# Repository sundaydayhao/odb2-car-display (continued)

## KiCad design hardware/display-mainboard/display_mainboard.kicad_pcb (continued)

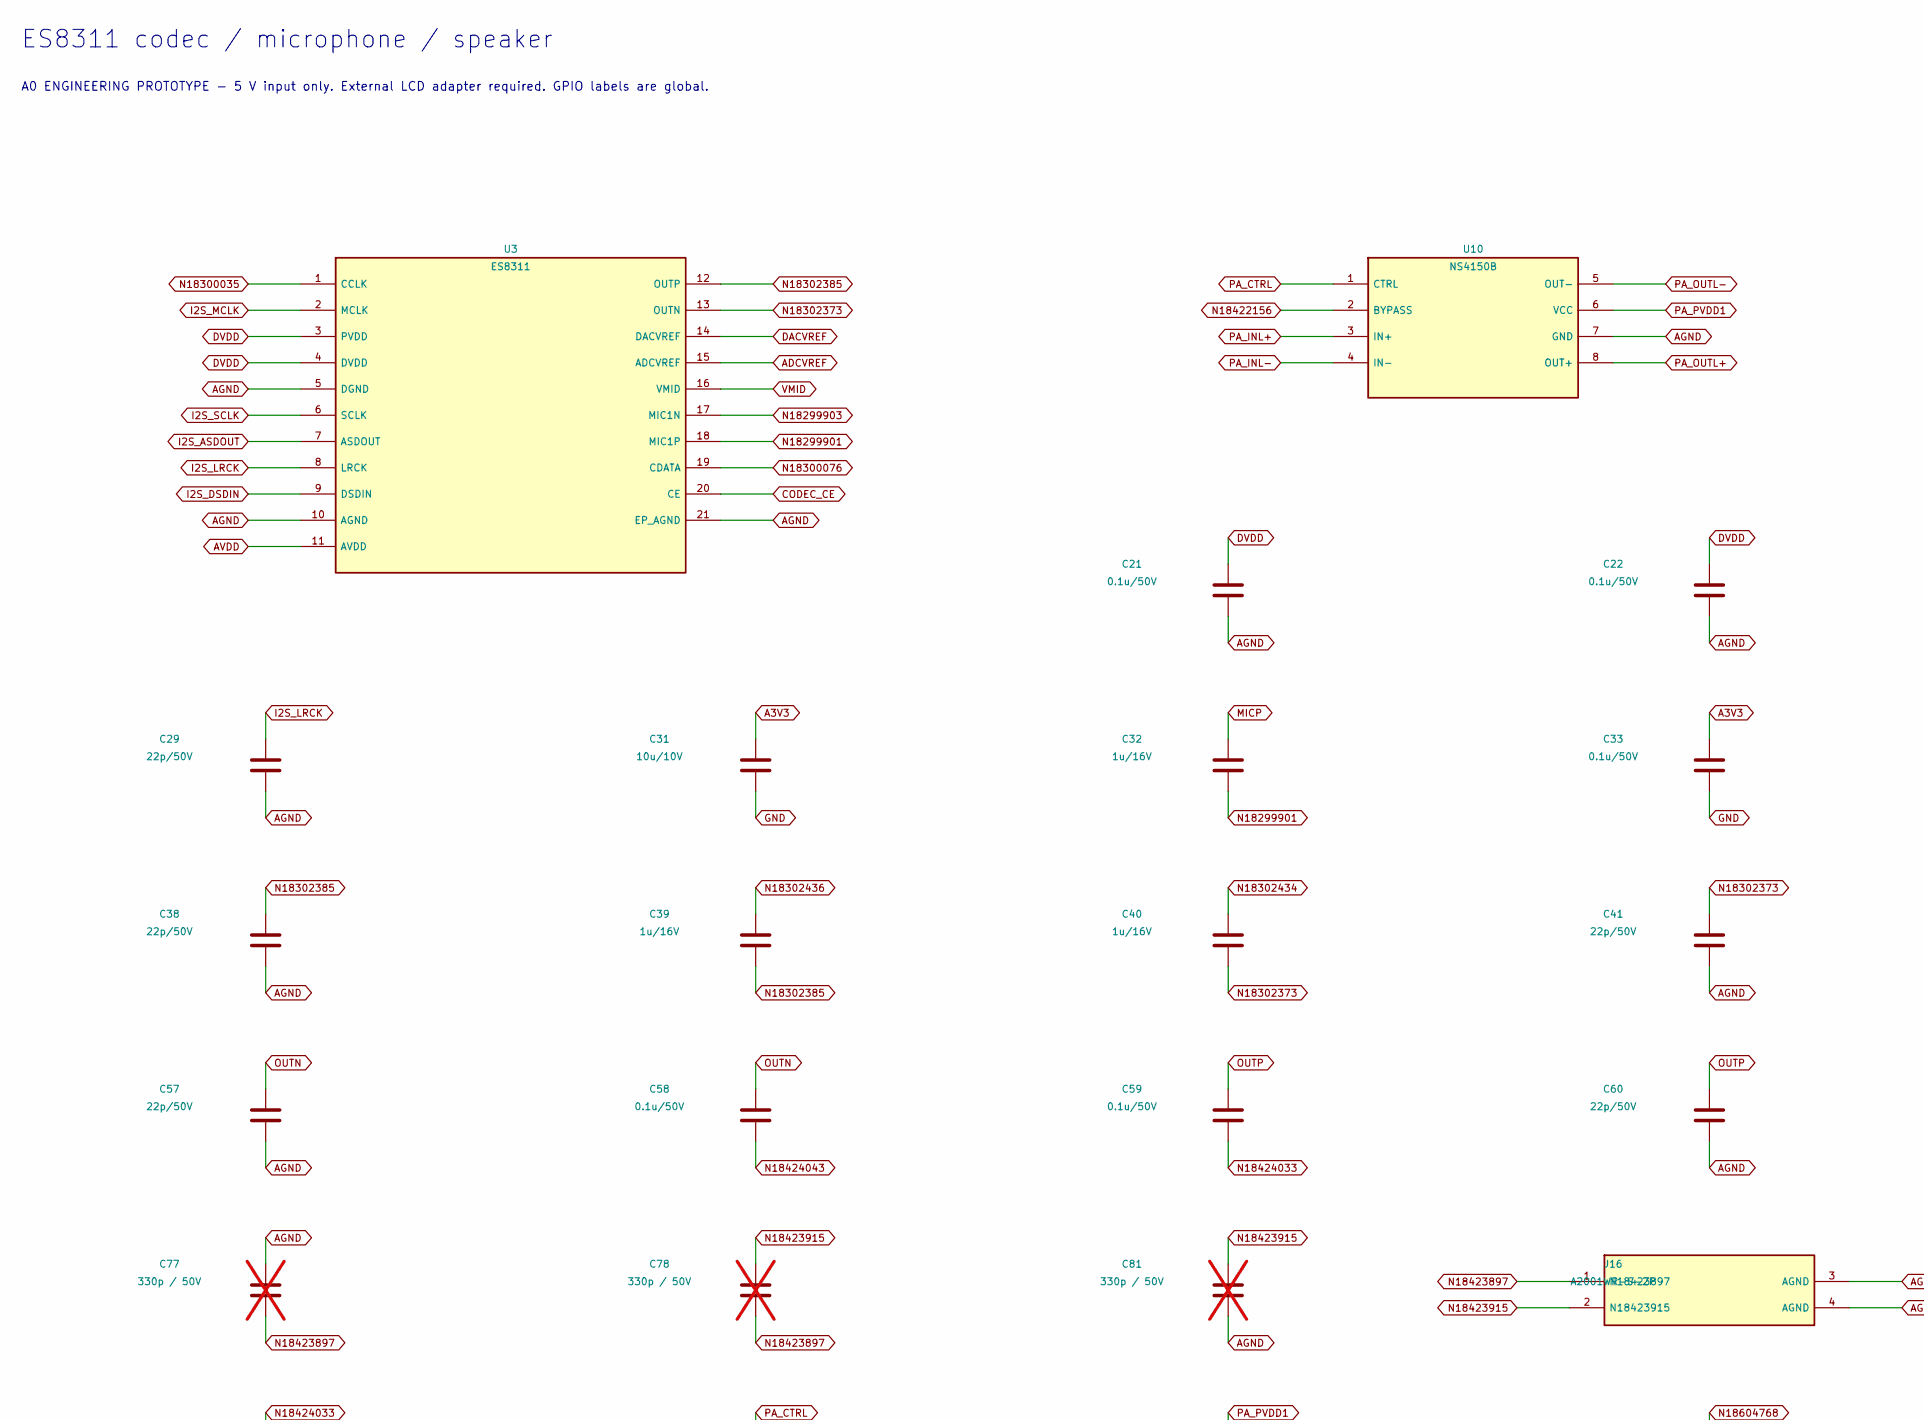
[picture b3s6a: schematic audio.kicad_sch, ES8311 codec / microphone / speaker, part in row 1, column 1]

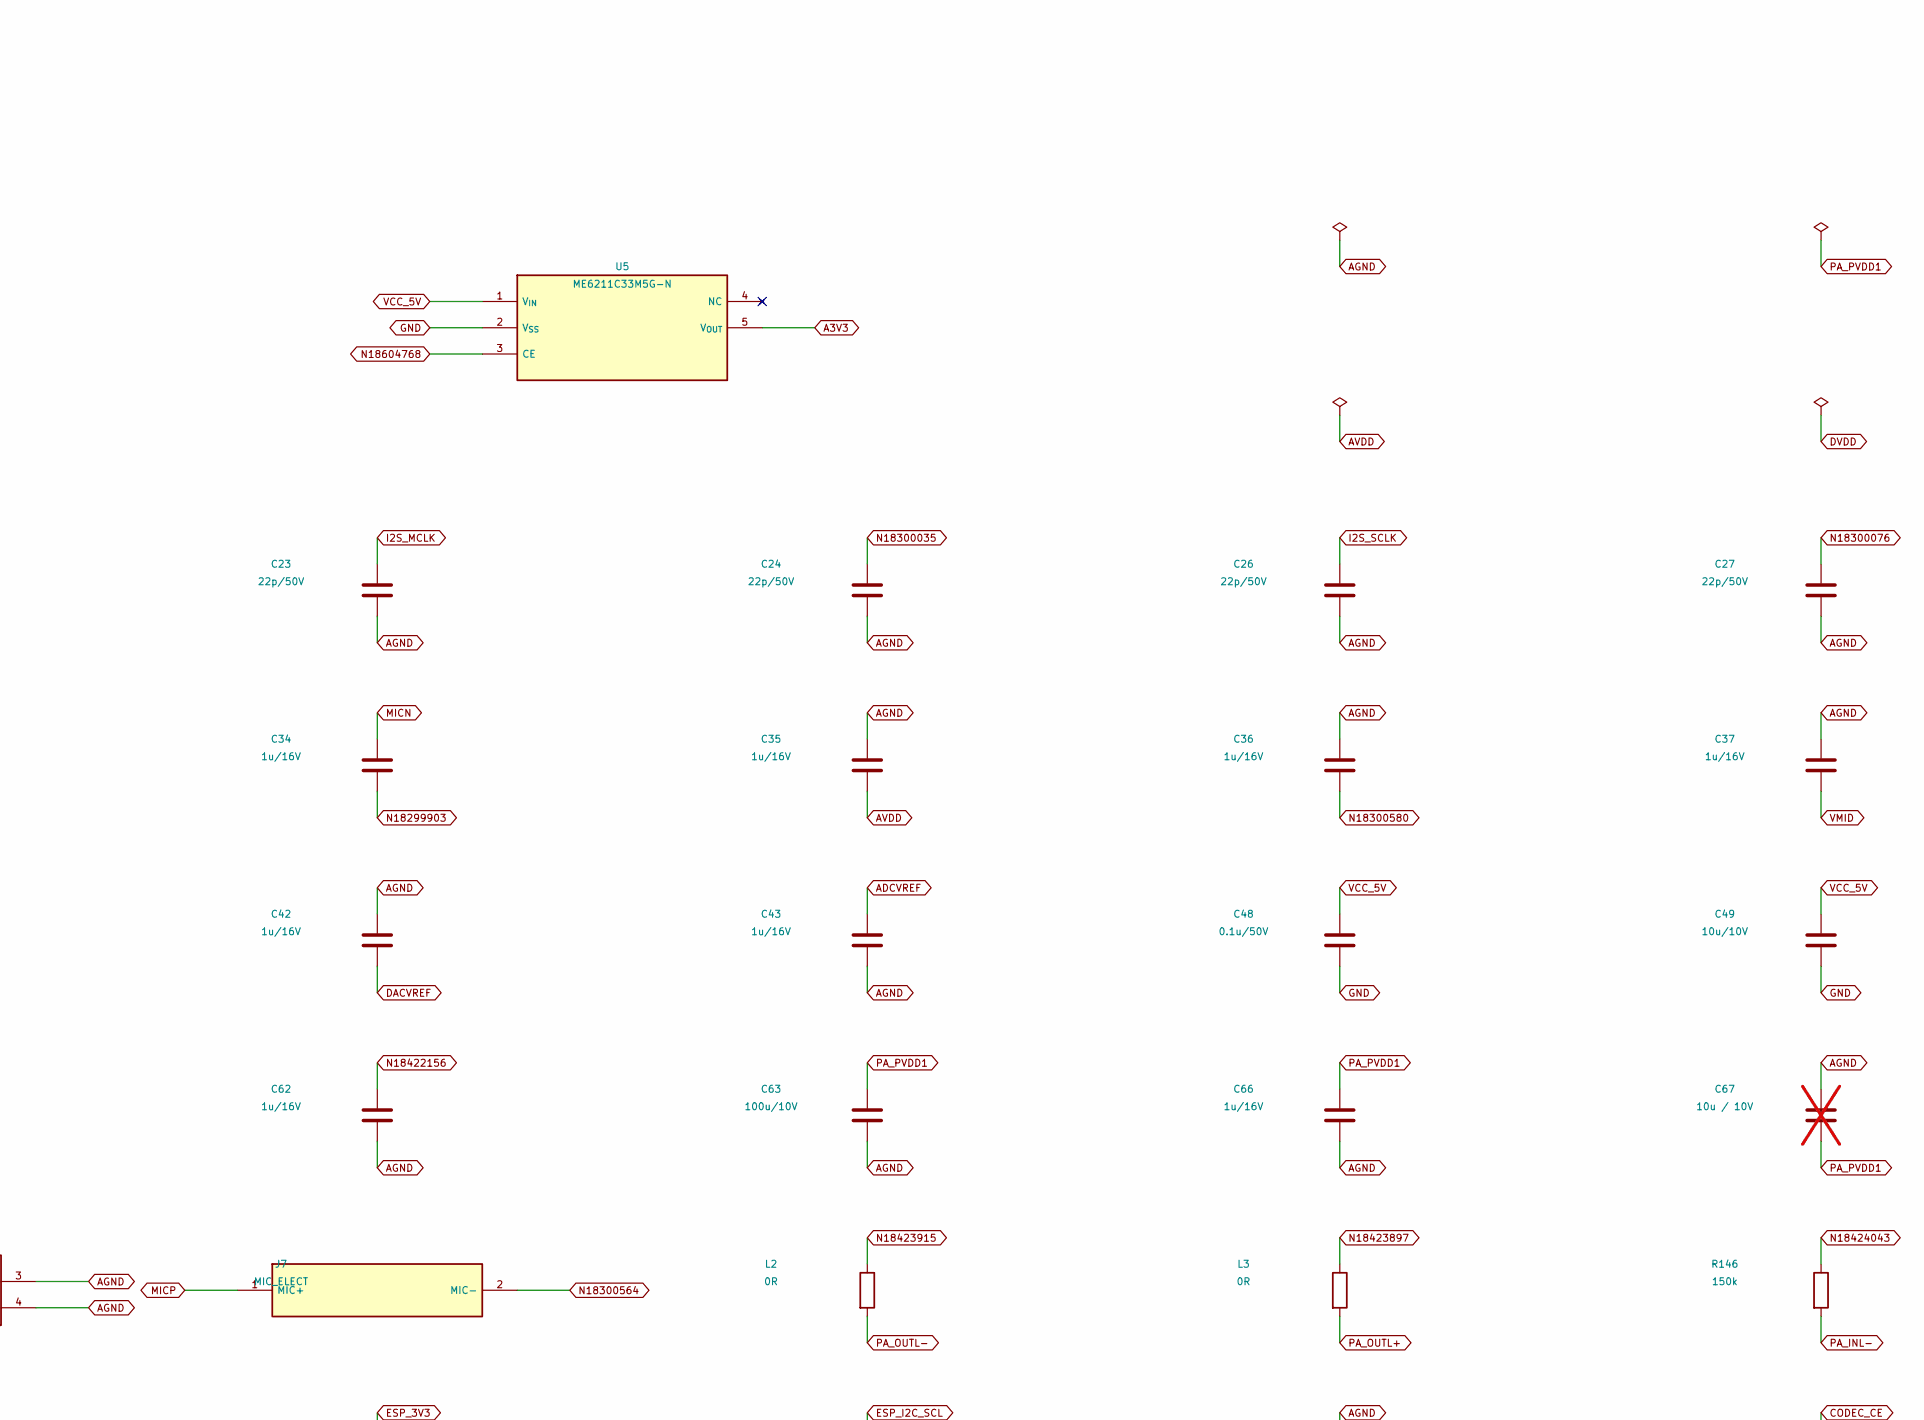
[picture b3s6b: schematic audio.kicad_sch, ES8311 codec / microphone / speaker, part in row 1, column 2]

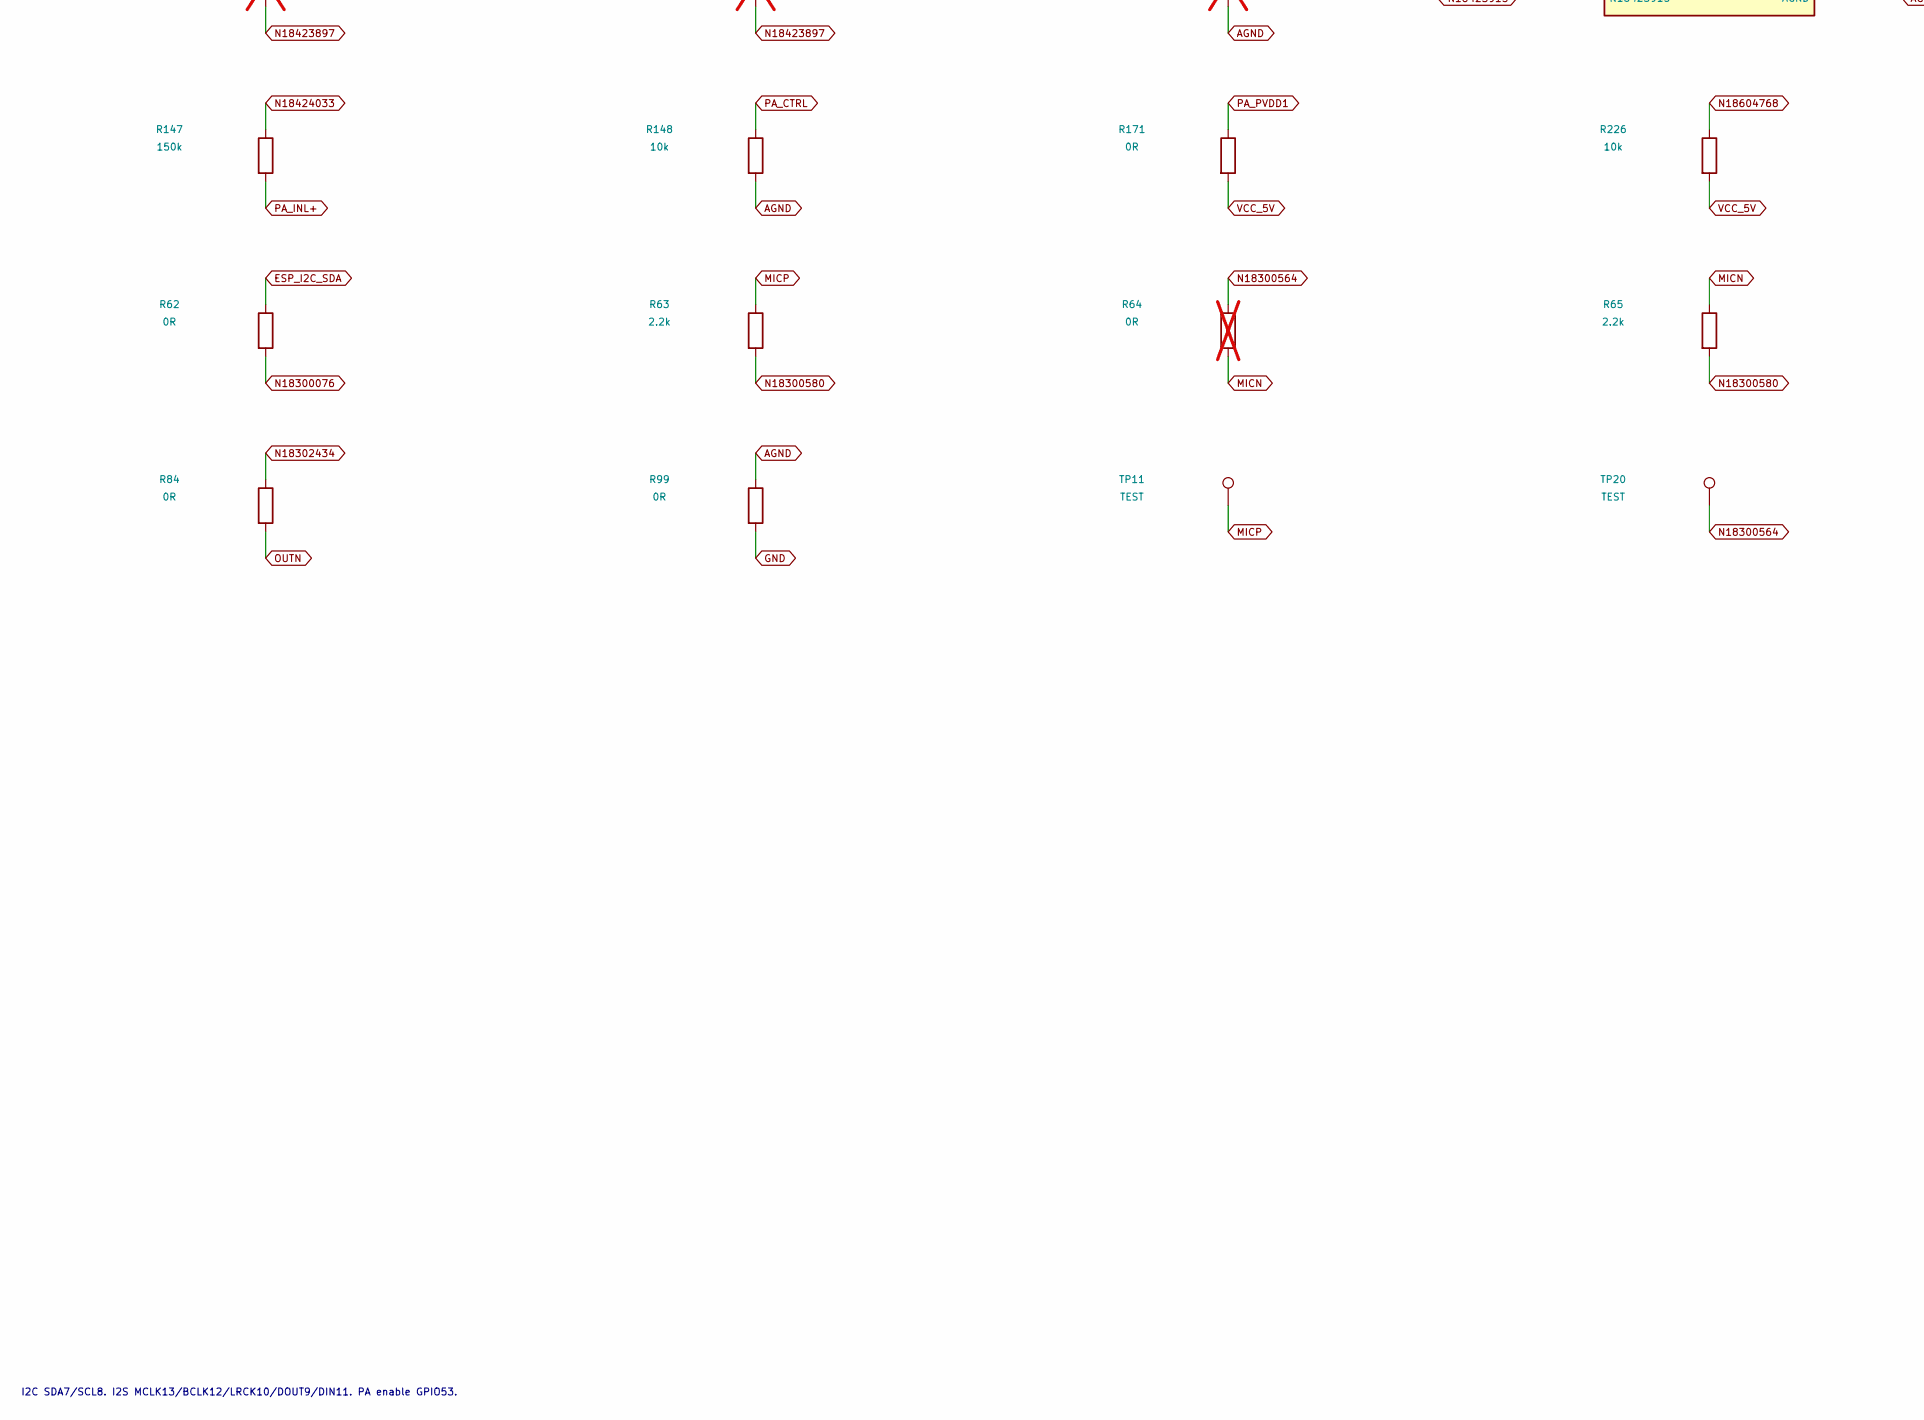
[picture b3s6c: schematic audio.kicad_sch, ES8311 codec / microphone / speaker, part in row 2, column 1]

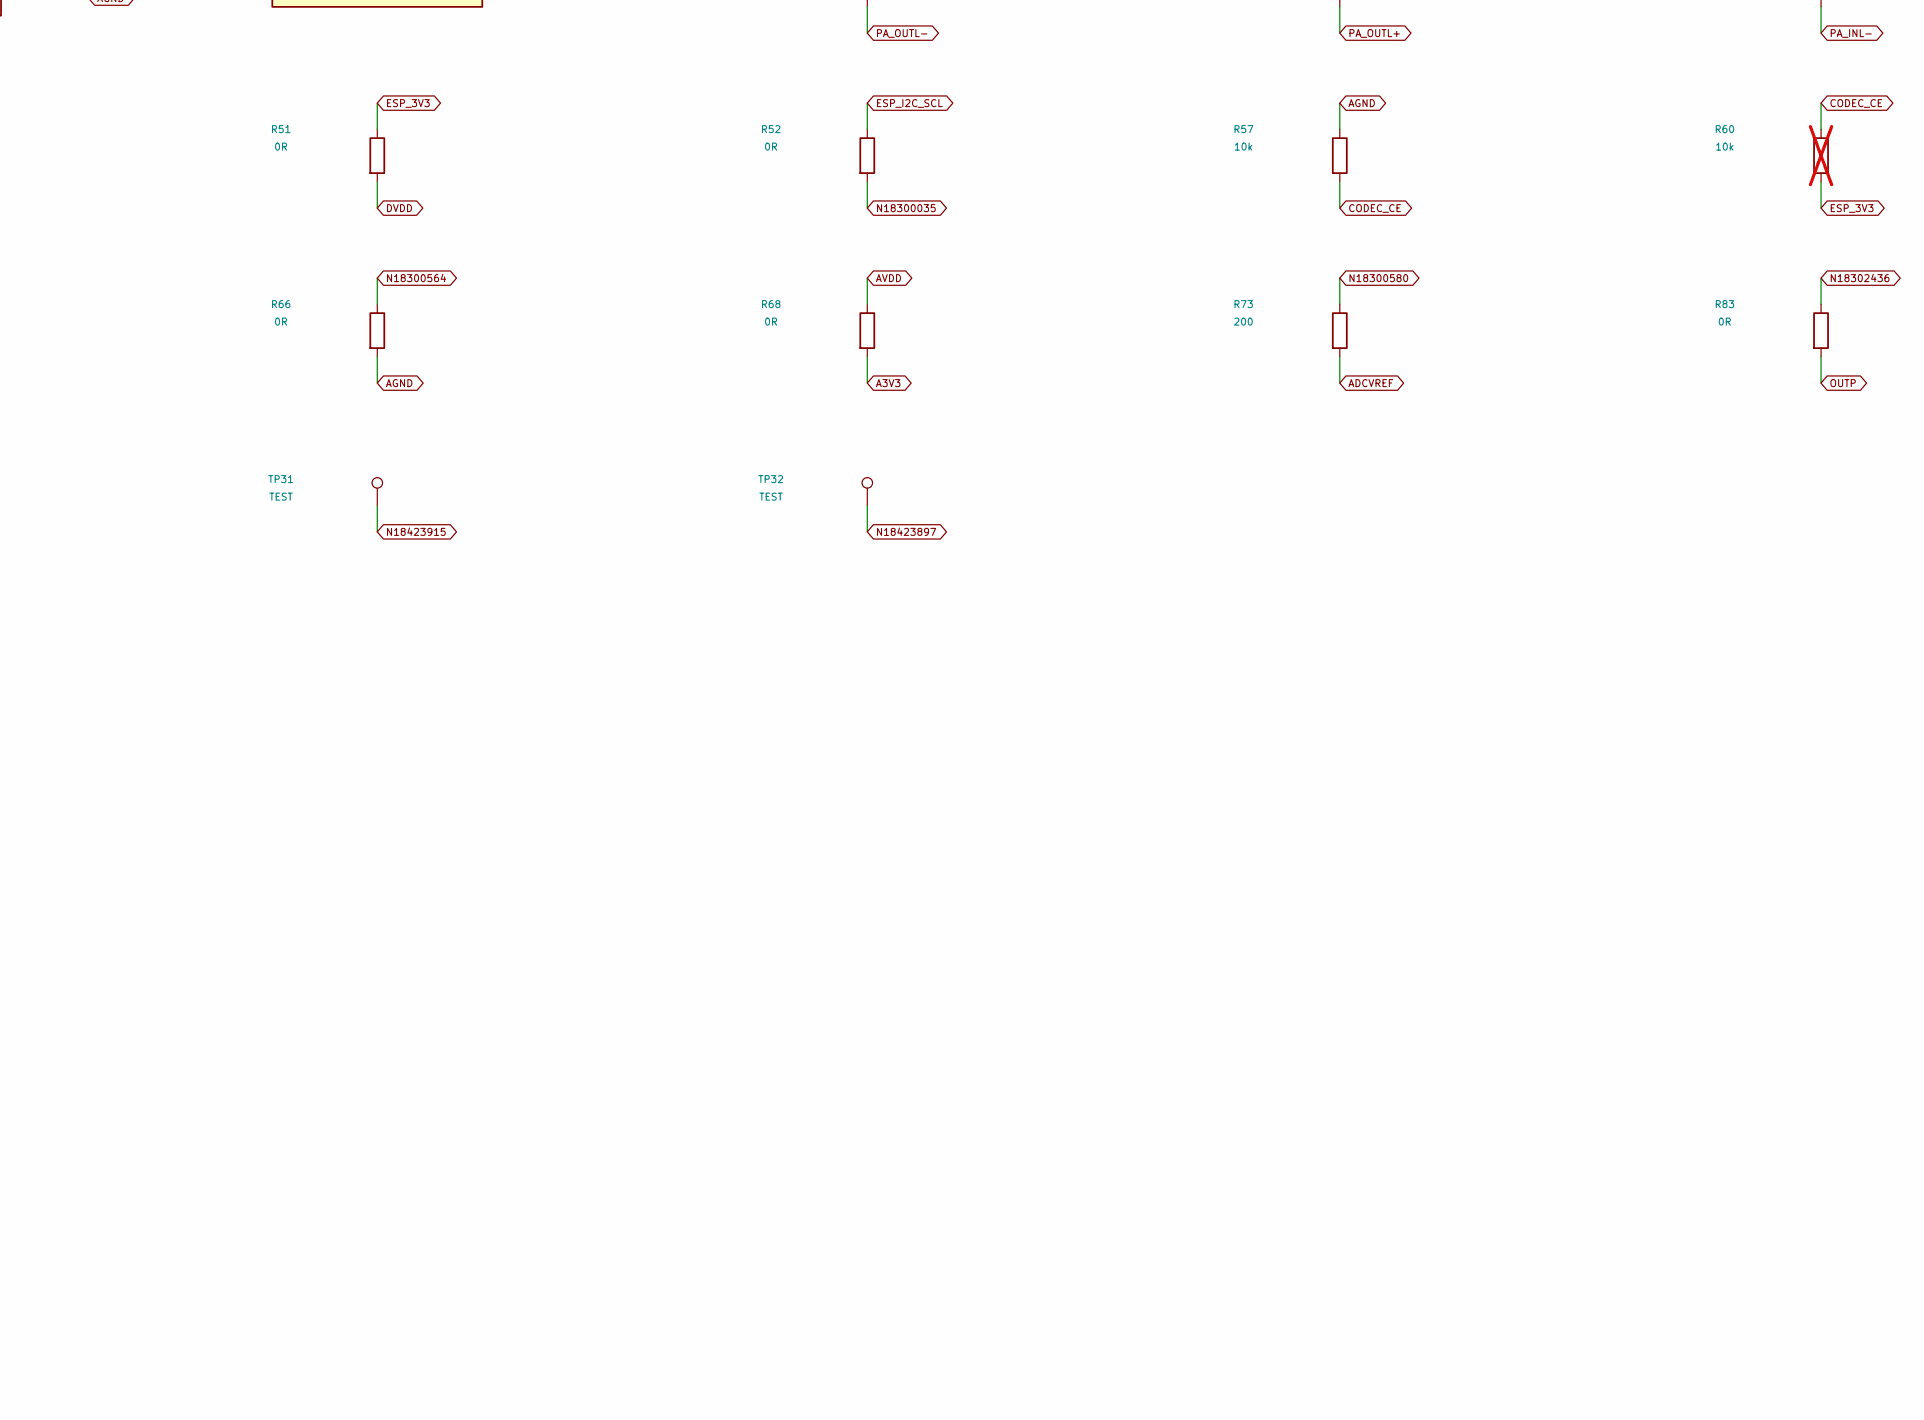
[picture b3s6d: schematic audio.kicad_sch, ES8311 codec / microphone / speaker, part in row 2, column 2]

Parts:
C21, C22, C33, C48, C58, C59: 0.1u/50V; C0402__d1e3d90c7a
C23, C24, C26, C27, C29, C38, C41, C57, C60: 22p/50V; C0402__d1e3d90c7a
C31, C49: 10u/10V; C0603__ebd4ddd8e4
C32, C34, C35, C36, C37, C39, C40, C42, C43, C62, C66: 1u/16V; C0402__d1e3d90c7a
C63: 100u/10V; C1206__33617ed97b
C67: 10u / 10V; C0603__ebd4ddd8e4; not fitted
C77, C78, C81: 330p / 50V; C0402__d1e3d90c7a; not fitted
J7: MIC_ELECT; MIC2_4_B4013AM422-042__565a78fc3e; MPN B4013AM422-042
J16: A2001WR-S-2P; CON2X1_2P0_SMT_PH2A-S-A__3aafb2579c; MPN A2001WR-S-2P
L2, L3: 0R; R0603__9e2f069e96
R51, R52, R62, R66, R68, R83, R84: 0R; R0402__c67fe31f10
R57, R148, R226: 10k; R0402__c67fe31f10
R60: 10k; R0402__c67fe31f10; not fitted
R63, R65: 2.2k; R0402__c67fe31f10
R64: 0R; R0402__c67fe31f10; not fitted
R73: 200; R0402__c67fe31f10
R99, R171: 0R; R0603__9e2f069e96
R146, R147: 150k; R0402__c67fe31f10
TP11, TP20, TP31, TP32: TEST; TPC1__9f0857eafe
U3: ES8311; QFN20_0P4_3__b115faeb64; MPN ES8311
U5: ME6211C33M5G-N; SOT23-5__cf243f5b81; MPN ME6211C33M5G-N
U10: NS4150B; SSOP8_0P65_5__11bfe522a4; MPN NS4150B

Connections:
A3V3: C31.1, C33.1, R68.2, U5.5 (V_{OUT})
ADCVREF: C43.1, R73.2, U3.15 (ADCVREF)
AGND: C21.2, C22.2, C23.2, C24.2, C26.2, C27.2, C29.2, C35.1, C36.1, C37.1, C38.2, C41.2, C42.1, C43.2, C57.2, C60.2, C62.2, C63.2, C66.2, C67.1, C77.1, C81.2, J16.3 (AGND), J16.4 (AGND), R57.1, R66.2, R99.1, R148.2, U3.5 (DGND), U3.10 (AGND), U3.21 (EP_AGND), U10.7 (GND)
AVDD: C35.2, R68.1, U3.11 (AVDD)
CODEC_CE: R57.2, R60.1, U3.20 (CE)
DACVREF: C42.2, U3.14 (DACVREF)
DVDD: C21.1, C22.1, R51.2, U3.3 (PVDD), U3.4 (DVDD)
ESP_3V3: R51.1, R60.2; also elsewhere on the board
ESP_I2C_SCL: R52.1; also elsewhere on the board
ESP_I2C_SDA: R62.1; also elsewhere on the board
I2S_ASDOUT: U3.7 (ASDOUT); also elsewhere on the board
I2S_DSDIN: U3.9 (DSDIN); also elsewhere on the board
I2S_LRCK: C29.1, U3.8 (LRCK); also elsewhere on the board
I2S_MCLK: C23.1, U3.2 (MCLK); also elsewhere on the board
I2S_SCLK: C26.1, U3.6 (SCLK); also elsewhere on the board
MICN: C34.1, R64.2, R65.1
MICP: C32.1, J7.1 (MIC+), R63.1, TP11.1
N18299901: C32.2, U3.18 (MIC1P)
N18299903: C34.2, U3.17 (MIC1N)
N18300035: C24.1, R52.2, U3.1 (CCLK)
N18300076: C27.1, R62.2, U3.19 (CDATA)
N18300564: J7.2 (MIC-), R64.1, R66.1, TP20.1
N18300580: C36.2, R63.2, R65.2, R73.1
N18302373: C40.2, C41.1, U3.13 (OUTN)
N18302385: C38.1, C39.2, U3.12 (OUTP)
N18302434: C40.1, R84.1
N18302436: C39.1, R83.1
N18422156: C62.1, U10.2 (BYPASS)
N18423897: C77.2, C78.2, J16.1 (N18423897), L3.1, TP32.1
N18423915: C78.1, C81.1, J16.2 (N18423915), L2.1, TP31.1
N18424033: C59.2, R147.1
N18424043: C58.2, R146.1
N18604768: R226.1, U5.3 (CE)
OUTN: C57.1, C58.1, R84.2
OUTP: C59.1, C60.1, R83.2
PA_CTRL: R148.1, U10.1 (CTRL); also elsewhere on the board
PA_INL+: R147.2, U10.3 (IN+)
PA_INL-: R146.2, U10.4 (IN-)
PA_OUTL+: L3.2, U10.8 (OUT+)
PA_OUTL-: L2.2, U10.5 (OUT-)
PA_PVDD1: C63.1, C66.1, C67.2, R171.1, U10.6 (VCC)
VCC_5V: C48.1, C49.1, R171.2, R226.2, U5.1 (V_{IN}); also elsewhere on the board
VMID: C37.2, U3.16 (VMID)

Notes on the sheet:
ES8311 codec / microphone / speaker
A0 ENGINEERING PROTOTYPE - 5 V input only. External LCD adapter required. GPIO labels are global.
I2C SDA7/SCL8. I2S MCLK13/BCLK12/LRCK10/DOUT9/DIN11. PA enable GPIO53.

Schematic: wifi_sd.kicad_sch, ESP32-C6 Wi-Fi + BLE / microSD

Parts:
C1: 10u/10V; C0603__1e7c8298a8
C2: 0.1u/50V; C0402__df1ad35910
C8: 1u/16V; C0402__df1ad35910
C14: 0.1u/50V; C0402_097d4b0b__328ab4e626
C15: 10u/10V; C0603_1ead970f__4ff9dc89d7
D3, D4, D5, D6, D7, D8, D10, D11: BSDFN2C031U; SOD882_55527cd7__832596a649; MPN BSDFN2C031U
J2: CON3X2; CON3X2_2P54__5709bcd3ab
J21: TF_CARD; TF_CARDA__9ea14d9044; MPN TF-1007F
Q8: AO3401A; SOT23-3__14816d8467; MPN AO3401A
R1, R3, R5, R6, R11, R12: 51k; R0402__6ca295102a
R4, R10: 10k; R0402__6ca295102a
R16, R17, R19, R21, R34, R36: 51k; R0402_097d4b0b__c1bfdfccc2
R229: 10k; R0402_097d4b0b__c1bfdfccc2
R230: 10k; R0402_097d4b0b__c1bfdfccc2; not fitted
TP3, TP4, TP5, TP6, TP7, TP8, TP9, TP13: TEST; TPC1_fd69f0aa__930cba657a
TP10, TP12, TP14, TP15, TP16, TP17, TP18, TP19: TEST; TPC1__56d55e75a0
U1: ESP32-C6-MINI-1; ESP32-C6-MINI-1__12b1335637; MPN ESP32-C6-MINI-1-N4

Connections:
C6_EN: C8.1, J2.1 (C6_EN), R4.1, U1.8 (EN); also elsewhere on the board
C6_IO8: R10.1, U1.22 (GPIO8)
C6_IO9: J2.6 (C6_IO9), U1.23 (GPIO9)
C6_U0RXD: J2.5 (C6_U0RXD), U1.30 (U0RXD)
C6_U0TXD: J2.3 (C6_U0TXD), U1.31 (U0TXD)
C6_WAKEUP: U1.5 (GPIO2); also elsewhere on the board
ESP_3V3: C1.1, C2.1, Q8.2 (S), R1.1, R3.1, R4.2, R5.1, R6.1, R10.2, R11.1, R12.1, R230.2, U1.3 (3V3); also elsewhere on the board
ESP_LDO_VO4: R17.1, R19.1, R21.1, R34.1, R36.1; also elsewhere on the board
SD1_CLK: D6.2 (A2), J21.5 (SD1_CLK), TP15.1; also elsewhere on the board
SD1_CMD: D4.2 (A2), J21.3 (SD1_CMD), R17.2, TP14.1; also elsewhere on the board
SD1_D0: D11.2 (A2), J21.7 (SD1_D0), R36.2, TP19.1; also elsewhere on the board
SD1_D1: D10.2 (A2), J21.8 (SD1_D1), R34.2, TP18.1; also elsewhere on the board
SD1_D2: D8.2 (A2), J21.1 (SD1_D2), R21.2, TP17.1; also elsewhere on the board
SD1_D3: D7.2 (A2), J21.2 (SD1_D3), R19.2, TP16.1; also elsewhere on the board
SD1_VDD: C14.1, C15.1, D3.2 (A2), J21.4 (SD1_VDD), Q8.3 (D), R16.1, TP13.1
SD2_CLK: R12.2, TP5.1, U1.25 (GPIO19); also elsewhere on the board
SD2_CMD: R11.2, TP4.1, U1.24 (GPIO18); also elsewhere on the board
SD2_D0: R6.2, TP9.1, U1.26 (GPIO20); also elsewhere on the board
SD2_D1: R5.2, TP8.1, U1.27 (GPIO21); also elsewhere on the board
SD2_D2: R3.2, TP7.1, U1.28 (GPIO22); also elsewhere on the board
SD2_D3: R1.2, TP6.1, U1.29 (GPIO23); also elsewhere on the board
SD_DET: D5.2 (A2), J21.9 (SD_DET), R16.2, TP10.1
SD_PWRN: Q8.1 (G), R229.2, R230.1; also elsewhere on the board

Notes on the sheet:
ESP32-C6 Wi-Fi + BLE / microSD
A6 MIPI SINGLE PCB - Regulated 5 V only. LCD / I2C CTP connect directly. GPIO labels are global.
microSD power switch (Q8 / GPIO45 active-low); C1 is C6 input decoupling. Retained in A4.

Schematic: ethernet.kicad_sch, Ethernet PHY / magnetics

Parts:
C1: 10u/10V; C0603__ebd4ddd8e4
C64, C68: 20p/50V; C0402__d1e3d90c7a
C108, C113, C114: 10u/10V; C0603_1ead970f__97efe4e755
C109, C111, C112, C115, C116: 0.1u/50V; C0402_097d4b0b__369f5d8838
J17: RJ45_HR913550A; RJ45_HR913129A__640c741964; MPN HR913550A
Q8: AO3401A; SOT23-3__4e657f28a8; MPN AO3401A
R139, R142, R143, R144, R150, R158, R161: 0R; R0402__c67fe31f10
R140, R141, R149, R155, R157, R169: 5.1k; R0402__c67fe31f10
R153, R154, R156, R164, R168: 5.1k; R0402__c67fe31f10; not fitted
R159: 10M; R0402__c67fe31f10; not fitted
R160: 1.5k; R0402__c67fe31f10; not fitted
R163: 1.5k; R0402__c67fe31f10
R165: 6.19k; R0402__c67fe31f10
R166, R167: 10k; R0402__c67fe31f10; not fitted
R181: 0R; R0603__9e2f069e96
R213: 0R; R0603_1ead970f__b0e26ec379
R222, R223: 1k; R0402_097d4b0b__cc2a00f46d
R229: 10k; R0402_097d4b0b__cc2a00f46d
R230: 10k; R0402_097d4b0b__cc2a00f46d; not fitted
U8: IP101GRI; QFN32_0P4_4_E2P75__7588c84cb7; MPN IP101GRI
Y3: 25MHz+/-10ppm; XTAL3225__86927bc1e6; MPN SX32Y025000BA1T

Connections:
25M_XI: R161.1, U8.2 (X1)
25M_XO: R158.1, U8.3 (X2)
COL: R149.2, R153.1, U8.4 (COL_RMII)
CRS: R154.1, R155.2, U8.20 (CRS_LEDMOD)
ESP_3V3: C1.1, Q8.2 (S), R213.1, R230.2; also elsewhere on the board
GND_RJ45_EARTH: J17.SHD1 (GND_RJ45_EARTH), J17.SHD2 (GND_RJ45_EARTH), R181.1
MDC: R160.2, U8.22 (MDC); also elsewhere on the board
MDIO: R163.2, U8.23 (MDIO); also elsewhere on the board
N18266990: C115.1, J17.4 (N18266990)
N18266994: C116.1, J17.5 (N18266994)
N18267072: J17.10 (N18267072), R223.1
N18267076: J17.11 (N18267076), R222.1
N18267340: R143.2, U8.17 (RXDV_CRS_DV)
N18267342: R144.2, U8.18 (RXD0)
N18267344: R150.2, U8.19 (RXD1)
N18267350: R139.2, U8.14 (RXCLK_50MCLKO)
N18267444: C111.1, C113.1, U8.28 (REGOUT)
N18267472: R142.2, U8.10 (TXCLK_50MCLKI)
N18379689: C64.1, R158.2, R159.1, Y3.1
N18379734: C68.1, R159.2, R161.2, Y3.3
PHY_3V3: C108.1, C109.1, C112.1, C114.1, J17.12 (PHY_3V3), R141.1, R149.1, R155.1, R157.1, R160.1, R163.1, R164.1, R167.1, R168.1, R213.2, U8.13 (VDD_IO), U8.31 (AVDD33)
PHY_AD0: R141.2, R222.2, U8.11 (LED0_PHYAD0)
PHY_AD3: J17.9 (PHY_AD3), R140.2, U8.12 (LED3_TESTON)
PHY_ISET: R165.1, U8.25 (ISET)
PHY_RSTN: R166.1, R167.2, U8.32 (RESET_N); also elsewhere on the board
PHY_TESTON: R164.2, U8.24 (TESTON)
RD+: J17.3 (RD+), U8.27 (MDI_RP)
RD-: J17.6 (RD-), U8.26 (MDI_RN)
RMII_CLK: R139.1, R142.1; also elsewhere on the board
RMII_RXD0: R144.1; also elsewhere on the board
RMII_RXD1: R143.1; also elsewhere on the board
RMII_RXDV: R150.1; also elsewhere on the board
RMII_TXD0: U8.9 (TXD0); also elsewhere on the board
RMII_TXD1: U8.8 (TXD1); also elsewhere on the board
RMII_TXEN: U8.5 (TXEN); also elsewhere on the board
RXER: R156.1, R157.2, U8.21 (RXER_INTR_32)
SD1_VDD: Q8.3 (D); also elsewhere on the board
SD_PWRN: Q8.1 (G), R229.2, R230.1; also elsewhere on the board
TD+: J17.1 (TD+), U8.30 (MDI_TP)
TD-: J17.2 (TD-), U8.29 (MDI_TN)
TXER: R168.2, R169.1, U8.1 (TXER_FXSD)

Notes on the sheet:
Ethernet PHY / magnetics
A0 ENGINEERING PROTOTYPE - 5 V input only. External LCD adapter required. GPIO labels are global.
Reference Ethernet interface retained. This display mainboard connects to the OBD node wirelessly.

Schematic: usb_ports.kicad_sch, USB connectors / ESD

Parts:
D17, D18, D19, D25: LESD5D5.0CT1G; SOD523__6a5b89da33; MPN LESD5D5.0CT1G
D21, D22: TPD1E05U06DPYR; TPD1E05U06_DPY0002A_TI; MPN TPD1E05U06DPYR; LCSC C436349
J18: USB-02; 292303-6__14239c459b; MPN 901-211A1021D10100
J19: USB_TYPEC_16P_F; USB_TYPEC_16P_F__bf963333d2; MPN TYPE-C-31-M-12
R183, R184: 5.1k; R0402__6ca295102a
R187: 0R; R0603__ca4d6f8805
R220, R221: 0R; R0402__6ca295102a

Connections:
N18256275: J19.6 (A5_CC1), R184.2
N18256281: J19.12 (B5_CC2), R183.2
USB1P1_N: D17.2 (A2), J19.7 (B7_DN2), J19.9 (A7_DN1); also elsewhere on the board
USB1P1_P: D18.2 (A2), J19.8 (A6_DP1), J19.10 (B6_DP2); also elsewhere on the board
USB_DM: R221.2; also elsewhere on the board
USB_DP: R220.2; also elsewhere on the board
VBUS_OUT: J18.1 (VBUS_OUT); also elsewhere on the board

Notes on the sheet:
USB-A HIGH-SPEED HOST / ESD
D21/D22: fitted TI TPD1E05U06DPYR, 5.5 V ultra-low-C USB ESD. Pin 1 = I/O; pin 2 = GND.
Regulated 5 V input protection (J22); not a USB power inlet.
J19 USB-C: P4 native USB Serial/JTAG (GPIO24/25). J18 USB-A: separate HS controller, fixed host.
D21/D22 use TI DPY0002A recommended lands (0.30 x 0.50 mm, 0.70 mm pitch). D25/D19 protect separate 5 V inputs.

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
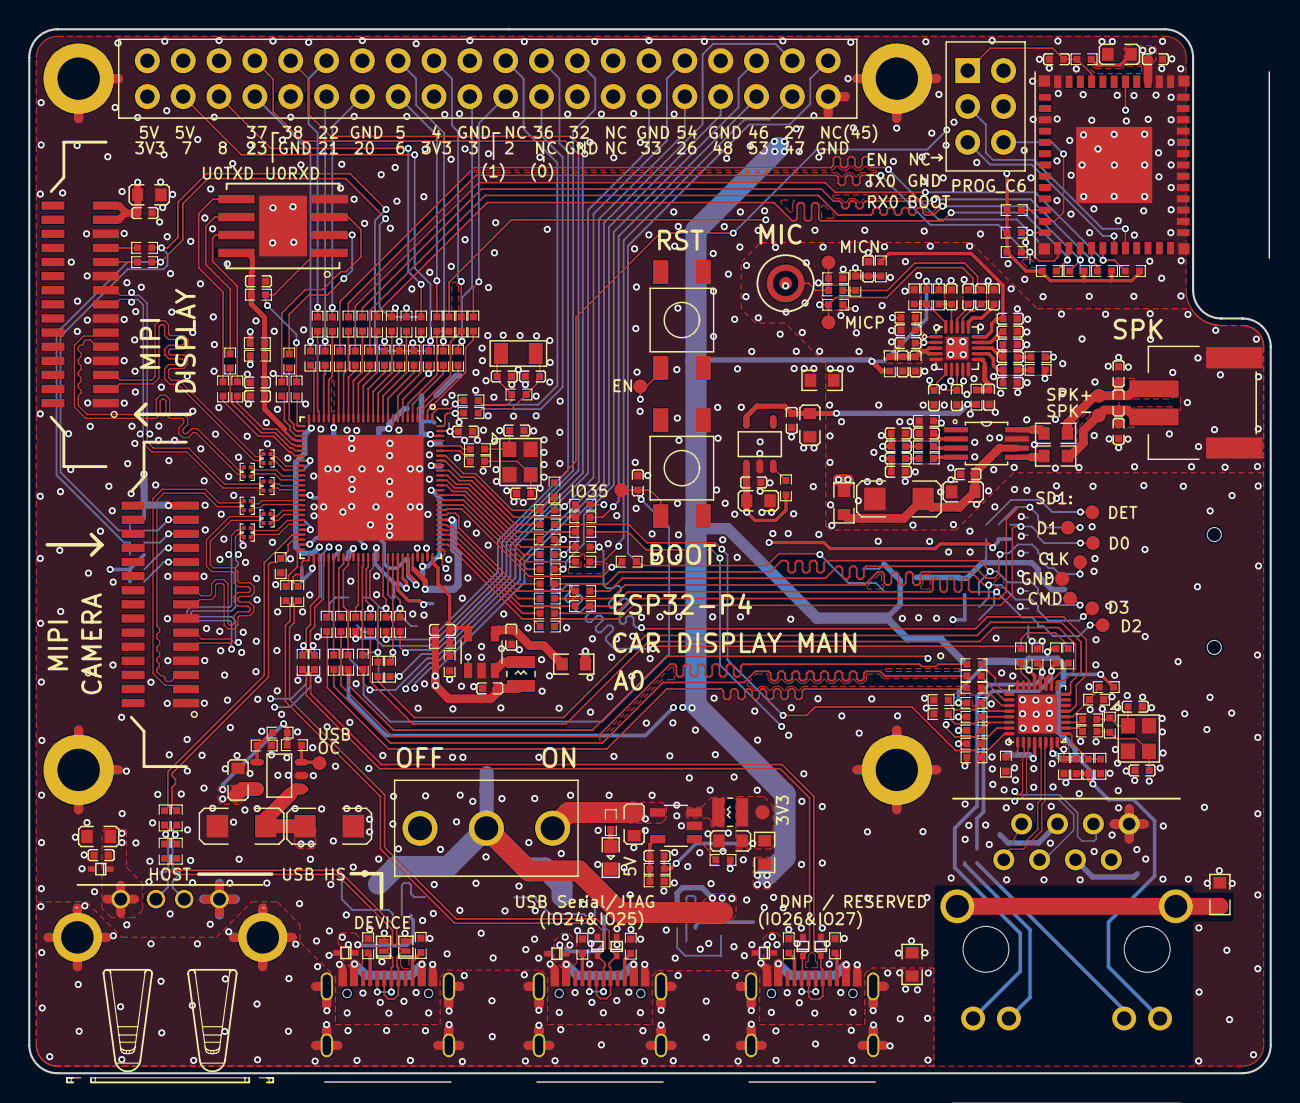
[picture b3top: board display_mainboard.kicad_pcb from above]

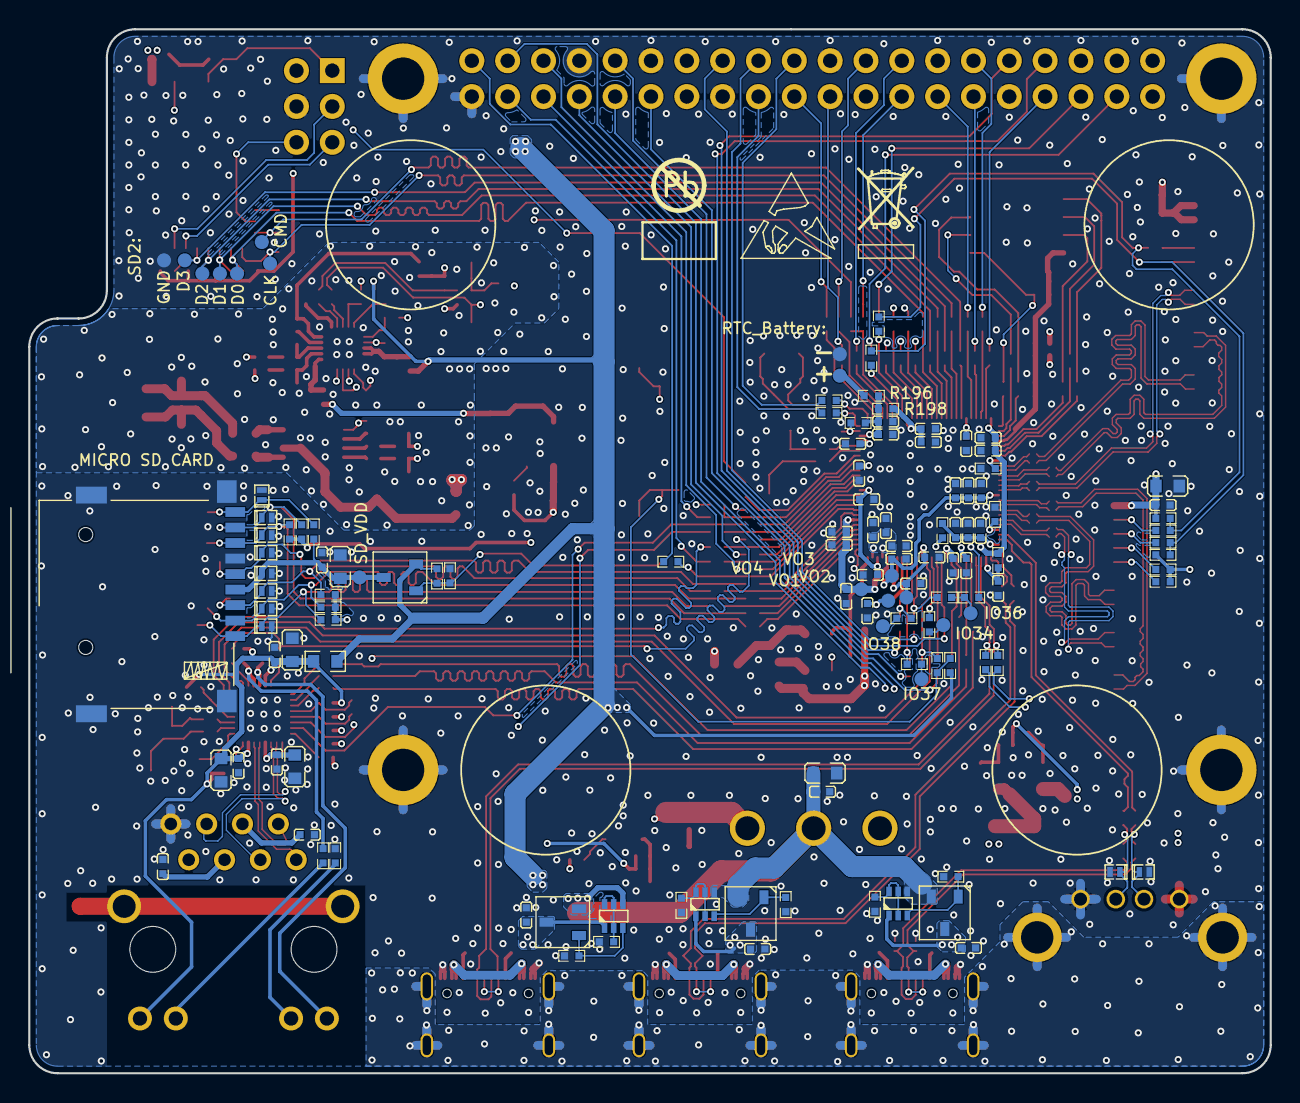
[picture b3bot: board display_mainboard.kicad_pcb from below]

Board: 4 copper layers, 88.0 x 74.0 mm, 408 parts (127 on the bottom side), 289 nets.

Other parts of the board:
D13, D20, D23, D24: LESD5D5.0CT1G; SOD523__e205ddb192
D14, D16: ESD7951ST5G; SOD882__9af2a781e3
J5: DSI_1-1734248-5; FFC_15P_1_MIPI__6b31759586
J15, J20: USB_TYPEC_16P_F; USB_TYPEC_16P_F__668d8992a3
R87, R89, R91, R92, R114, R115, R117, R132, R133, R135, R178, R179: 0R; R0402__c67fe31f10
R113, R131: 33; R0402__c67fe31f10
R180, R182, R185, R186: 5.1k; R0402__c67fe31f10

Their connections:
DSI_A_CLKN: J5.5; also elsewhere on the board
DSI_A_CLKP: J5.6; also elsewhere on the board
DSI_A_DATA0N: J5.8; also elsewhere on the board
DSI_A_DATA0P: J5.9; also elsewhere on the board
DSI_A_DATA1N: J5.2; also elsewhere on the board
DSI_A_DATA1P: J5.3; also elsewhere on the board
ESP_3V3: J5.14, J5.15; also elsewhere on the board
GPIO26: R113.1; also elsewhere on the board
GPIO27: R131.1; also elsewhere on the board
GPIO28: R114.1; also elsewhere on the board
GPIO29: R132.1; also elsewhere on the board
GPIO30: R115.1; also elsewhere on the board
GPIO31: R133.1; also elsewhere on the board
GPIO34: R117.1; also elsewhere on the board
GPIO35: R135.1; also elsewhere on the board
GPIO49: R92.1; also elsewhere on the board
GPIO50: R91.1; also elsewhere on the board
GPIO51: R89.1; also elsewhere on the board
GPIO52: R87.1; also elsewhere on the board
MDC: R133.2; also elsewhere on the board
MDIO: R87.2; also elsewhere on the board
N18255493: J15.6, R180.2
N18255499: J15.12, R182.2
N18405255: J20.6, R185.2
N18405261: J20.12, R186.2
N18412230: J5.11; also elsewhere on the board
N18412242: J5.12; also elsewhere on the board
PHY_RSTN: R89.2; also elsewhere on the board
RMII_CLK: R91.2; also elsewhere on the board
RMII_RXD0: R132.2; also elsewhere on the board
RMII_RXD1: R115.2; also elsewhere on the board
RMII_RXDV: R114.2; also elsewhere on the board
RMII_TXD0: R117.2; also elsewhere on the board
RMII_TXD1: R135.2; also elsewhere on the board
RMII_TXEN: R92.2; also elsewhere on the board
USB0_5V: D20.2, J20.3, J20.4, J20.13, J20.14; also elsewhere on the board
USB1P1_N_2: D24.2, J20.7, J20.9, R113.2
USB1P1_P_2: D23.2, J20.8, J20.10, R131.2
USB2_5V: D13.2, J15.3, J15.4, J15.13, J15.14; also elsewhere on the board
USB_DM_C: D14.2, J15.7, J15.9, R178.1
USB_DP_C: D16.2, J15.8, J15.10, R179.1
